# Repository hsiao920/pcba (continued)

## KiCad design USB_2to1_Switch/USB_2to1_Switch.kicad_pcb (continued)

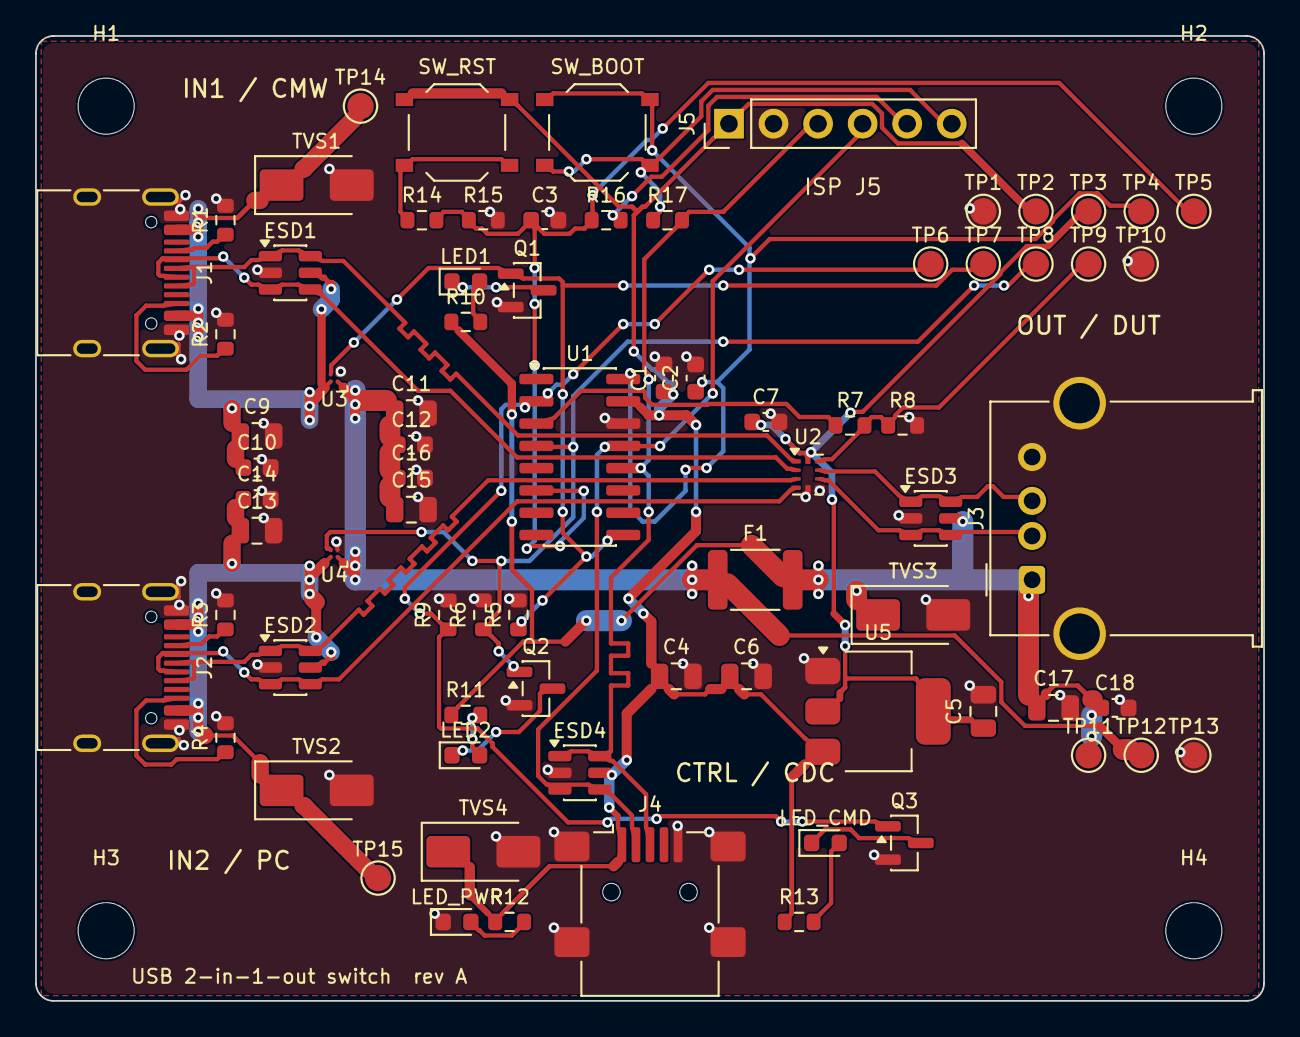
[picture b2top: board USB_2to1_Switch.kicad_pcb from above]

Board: 2 copper layers, 70.0 x 55.0 mm, 81 parts (0 on the bottom side), 36 nets.

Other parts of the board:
H1, H2, H3, H4: M3; MountingHole_3.2mm_M3

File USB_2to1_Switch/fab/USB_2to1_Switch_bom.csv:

"Refs","Value","Footprint","Qty","DNP"
"C1","0.1u","Capacitor_SMD:C_0603_1608Metric","1",""
"C2","0.1u","Capacitor_SMD:C_0603_1608Metric","1",""
"C3","0.1u","Capacitor_SMD:C_0603_1608Metric","1",""
"C4","10u","Capacitor_SMD:C_0805_2012Metric","1",""
"C5","22u","Capacitor_SMD:C_0805_2012Metric","1",""
"C6","10u","Capacitor_SMD:C_0805_2012Metric","1",""
"C7","0.1u","Capacitor_SMD:C_0603_1608Metric","1",""
"C9","10u","Capacitor_SMD:C_0805_2012Metric","1",""
"C10","0.1u","Capacitor_SMD:C_0603_1608Metric","1",""
"C11","10u","Capacitor_SMD:C_0805_2012Metric","1",""
"C12","0.1u","Capacitor_SMD:C_0603_1608Metric","1",""
"C13","10u","Capacitor_SMD:C_0805_2012Metric","1",""
"C14","0.1u","Capacitor_SMD:C_0603_1608Metric","1",""
"C15","10u","Capacitor_SMD:C_0805_2012Metric","1",""
"C16","0.1u","Capacitor_SMD:C_0603_1608Metric","1",""
"C17","10u","Capacitor_SMD:C_0805_2012Metric","1",""
"C18","0.1u","Capacitor_SMD:C_0603_1608Metric","1",""
"ESD1","USBLC6-2SC6","Package_TO_SOT_SMD:SOT-23-6","1",""
"ESD2","USBLC6-2SC6","Package_TO_SOT_SMD:SOT-23-6","1",""
"ESD3","USBLC6-2SC6","Package_TO_SOT_SMD:SOT-23-6","1",""
"ESD4","USBLC6-2SC6","Package_TO_SOT_SMD:SOT-23-6","1",""
"F1","PTC 2.5A hold / 5A trip (MF-MSMF250)","Fuse:Fuse_1812_4532Metric","1",""
"J1","Type-C receptacle (UFP)","Connector_USB:USB_C_Receptacle_HRO_TYPE-C-31-M-12","1",""
"J2","Type-C receptacle (UFP)","Connector_USB:USB_C_Receptacle_HRO_TYPE-C-31-M-12","1",""
"J3","USB-A receptacle","Connector_USB:USB_A_Molex_67643_Horizontal","1",""
"J4","Mini-USB-B receptacle","Connector_USB:USB_Mini-B_Lumberg_2486_01_Horizontal","1",""
"J5","ISP 1x6","Connector_PinHeader_2.54mm:PinHeader_1x06_P2.54mm_Vertical","1",""
"LED1","green","LED_SMD:LED_0603_1608Metric","1",""
"LED2","yellow","LED_SMD:LED_0603_1608Metric","1",""
"LED_CMD?","blue","LED_SMD:LED_0603_1608Metric","1",""
"LED_PWR?","red","LED_SMD:LED_0603_1608Metric","1",""
"Q1","2N7002","Package_TO_SOT_SMD:SOT-23","1",""
"Q2","2N7002","Package_TO_SOT_SMD:SOT-23","1",""
"Q3","2N7002","Package_TO_SOT_SMD:SOT-23","1",""
"R1","5.1k","Resistor_SMD:R_0603_1608Metric","1",""
"R2","5.1k","Resistor_SMD:R_0603_1608Metric","1",""
"R3","5.1k","Resistor_SMD:R_0603_1608Metric","1",""
"R4","5.1k","Resistor_SMD:R_0603_1608Metric","1",""
"R5","1.5k","Resistor_SMD:R_0603_1608Metric","1",""
"R6","1.5k","Resistor_SMD:R_0603_1608Metric","1",""
"R7","5.1k","Resistor_SMD:R_0603_1608Metric","1",""
"R8","10k","Resistor_SMD:R_0603_1608Metric","1",""
"R9","10k","Resistor_SMD:R_0603_1608Metric","1",""
"R10","1k","Resistor_SMD:R_0603_1608Metric","1",""
"R11","1k","Resistor_SMD:R_0603_1608Metric","1",""
"R12","1k","Resistor_SMD:R_0603_1608Metric","1",""
"R13","1k","Resistor_SMD:R_0603_1608Metric","1",""
"R14","1k","Resistor_SMD:R_0603_1608Metric","1",""
"R15","10k","Resistor_SMD:R_0603_1608Metric","1",""
"R16","100","Resistor_SMD:R_0603_1608Metric","1",""
"R17","10k","Resistor_SMD:R_0603_1608Metric","1",""
"SW_BOOT?","BOOT","Button_Switch_SMD:SW_Push_1P1T_XKB_TS-1187A","1",""
"SW_RST?","RST","Button_Switch_SMD:SW_Push_1P1T_XKB_TS-1187A","1",""
"TP1","TP_GND","TestPoint:TestPoint_Pad_D1.5mm","1",""
"TP2","TP_+5V","TestPoint:TestPoint_Pad_D1.5mm","1",""
"TP3","TP_+3V3","TestPoint:TestPoint_Pad_D1.5mm","1",""
"TP4","TP_V33","TestPoint:TestPoint_Pad_D1.5mm","1",""
"TP5","TP_RST","TestPoint:TestPoint_Pad_D1.5mm","1",""
"TP6","TP_CMD","TestPoint:TestPoint_Pad_D1.5mm","1",""
"TP7","TP_ON1","TestPoint:TestPoint_Pad_D1.5mm","1",""
"TP8","TP_ON2","TestPoint:TestPoint_Pad_D1.5mm","1",""
"TP9","TP_S","TestPoint:TestPoint_Pad_D1.5mm","1",""
"TP10","TP_GND","TestPoint:TestPoint_Pad_D1.5mm","1",""
"TP11","TP_OUT_VBUS","TestPoint:TestPoint_Pad_D1.5mm","1",""
"TP12","TP_VSW","TestPoint:TestPoint_Pad_D1.5mm","1",""
"TP13","TP_GND","TestPoint:TestPoint_Pad_D1.5mm","1",""
"TP14","TP_VBUS1","TestPoint:TestPoint_Pad_D1.5mm","1",""
"TP15","TP_VBUS2","TestPoint:TestPoint_Pad_D1.5mm","1",""
"TVS1","SMAJ5.0A","Diode_SMD:D_SMA","1",""
"TVS2","SMAJ5.0A","Diode_SMD:D_SMA","1",""
"TVS3","SMAJ5.0A","Diode_SMD:D_SMA","1",""
"TVS4","SMAJ5.0A","Diode_SMD:D_SMA","1",""
"U1","CH552G","Package_SO:SOIC-16_3.9x9.9mm_P1.27mm","1",""
"U2","TS3USB221A","Package_DFN_QFN:Texas_UQFN-10_1.5x2mm_P0.5mm","1",""
"U3","TPS22916BYFP","USB2to1:TPS22916_YFP_DSBGA-4_0.4mm","1",""
"U4","TPS22916BYFP","USB2to1:TPS22916_YFP_DSBGA-4_0.4mm","1",""
"U5","AMS1117-3.3","Package_TO_SOT_SMD:SOT-223-3_TabPin2","1",""

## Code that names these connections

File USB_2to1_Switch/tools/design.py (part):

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              ("6", "RST"), ("7", "P3.0/RXD"), ("8", "P3.1/TXD")],
             [("16", "V33"), ("15", "VCC"), ("14", "GND"), ("13", "P3.7/UDM"), ("12", "P3.6/UDP"),
              ("11", "P3.4"), ("10", "P3.3/INT1"), ("9", "P1.1")]),
        pins={"1": None, "2": "CMD", "3": "S_DRV", "4": "ON2", "5": None, "6": "RST", "7": None, "8": None,
              "9": "ON1", "10": None, "11": None, "12": "D4P", "13": "D4N", "14": "GND", "15": "+5V", "16": "V33"},
        note="CH552G SOP16 pinout per WCH CH552 datasheet (md pin table was wrong)"))
    P.append(dict(
        ref="U2", value="TS3USB221A", fp=("Package_DFN_QFN", "Texas_UQFN-10_1.5x2mm_P0.5mm"),
        sym=([("1", "1D+"), ("2", "1D-"), ("3", "2D+"), ("4", "2D-"), ("5", "GND")],
             [("10", "VCC"), ("9", "S"), ("8", "D+"), ("7", "D-"), ("6", "OE")]),
        pins={"1": "D1P", "2": "D1N", "3": "D2P", "4": "D2N", "5": "GND", "6": "GND", "7": "D3N", "8": "D3P",
              "9": "S", "10": "+3V3"},
        note="OE is active-LOW: tied to GND (md said 3.3V which disables the switch)"))
    for ref, vin, on, note in (("U3", "VBUS1", "ON1", "CH1 load switch"), ("U4", "VBUS2", "ON2", "CH2 load switch")):
        P.append(dict(
            ref=ref, value="TPS22916BYFP", fp=("USB2to1", "TPS22916_YFP_DSBGA-4_0.4mm"),
            sym=([("A2", "VIN"), ("B2", "ON")], [("A1", "VOUT"), ("B1", "GND")]),
            pins={"A2": vin, "B2": on, "A1": "VSW", "B1": "GND"}, note=note + " (0.4mm pitch WCSP)"))
    P.append(dict(
        ref="U5", value="AMS1117-3.3", fp=("Package_TO_SOT_SMD", "SOT-223-3_TabPin2"),
        sym=([("3", "VIN"), ("1", "GND")], [("2", "VOUT")]),
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    P.append(typec("J2", "VBUS2", "D2P", "D2N", "J2_CC1", "J2_CC2", "IN2 / PC"))
    P.append(dict(ref="J3", value="USB-A receptacle", fp=("Connector_USB", "USB_A_Molex_67643_Horizontal"),
                  sym=([("1", "VBUS"), ("2", "D-"), ("3", "D+"), ("4", "GND")], [("SH", "SHIELD")]),
                  pins={"1": "OUT_VBUS", "2": "D3N", "3": "D3P", "4": "GND", "SH": "GND"}, note="OUT / DUT"))
    P.append(dict(ref="J4", value="Mini-USB-B receptacle", fp=("Connector_USB", "USB_Mini-B_Lumberg_2486_01_Horizontal"),
                  sym=([("1", "VBUS"), ("2", "D-"), ("3", "D+"), ("4", "ID"), ("5", "GND")], [("SH", "SHIELD")]),
                  pins={"1": "+5V", "2": "D4N", "3": "D4P", "4": None, "5": "GND", "SH": "GND"}, note="CTRL / CDC"))
    P.append(dict(ref="J5", value="ISP 1x6", fp=("Connector_PinHeader_2.54mm", "PinHeader_1x06_P2.54mm_Vertical"),
                  sym=([("1", "5V"), ("2", "GND"), ("3", "D+"), ("4", "D-"), ("5", "RST"), ("6", "BOOT")], []),
                  pins={"1": "+5V", "2": "GND", "3": "D4P", "4": "D4N", "5": "RST_J5", "6": "BOOT"}, note=""))

    # ------------------------------------------------------------------ ESD / TVS
    for ref, dp, dn, vb in (("ESD1", "D1P", "D1N", "VBUS1"), ("ESD2", "D2P", "D2N", "VBUS2"),
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        P.append(rc(ref, v, a, b, fp=fp))
    # ------------------------------------------------------------------ output current limit (resettable fuse)
    P.append(dict(ref="F1", value="PTC 2.5A hold / 5A trip (MF-MSMF250)", fp=("Fuse", "Fuse_1812_4532Metric"),
                  sym=([("1", "1")], [("2", "2")]), pins={"1": "VSW", "2": "OUT_VBUS"},
                  note="J3 output short-circuit protection; VSW = load-switch side, OUT_VBUS = connector side"))
    # ------------------------------------------------------------------ test points
    for i, net in enumerate(TP_NETS, 1):
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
